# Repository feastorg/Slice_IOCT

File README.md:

# Slice_IOCT

Industrial digital I/O slice for BREAD: four 12–24 V inputs and four
solid-state relay outputs, for sensors and actuators on a 24 V field supply.

An Arduino Nano on the 10-pin slice bus (G3, Slice Interface 1), 70 × 100 mm,
two layers. Hardware revision r2.

## Introduction

The slice works like a small PLC I/O module. Each input reads a field signal
through an optocoupler with a switching threshold; each output is a photo-MOSFET
relay that switches a load from the field supply or acts as a dry contact. A low
level on the bus e-stop line turns every output off in hardware, whatever the
firmware does.

## Usage

### Inputs (J3)

Each input has three terminals: `INx+`, `INx-` and `GND`.

- **Floating (isolated):** connect the sensor's output between `INx+` and
  `INx-`. The source must provide its own return path.
- **Board-referenced:** link `INx-` to the `GND` terminal beside it and drive
  `INx+` against board ground.

An input reads OFF below about 7 V and ON from 11 V; it is rated to 30 V. A
reversed input does no harm. The Nano reads IN1–IN4 on D9, D8, D7 and D6, high
when the input is on.

### Outputs (J2)

Each output has three terminals: `OUTx-`, `OUTx+` and `VF` (VFIELD).

- **Wet contact:** link `VF` to `OUTx+` (the next terminal) and wire the load
  from `OUTx-` to `GND` on J1.
- **Dry contact:** leave `VF` unconnected and use `OUTx+` / `OUTx-` as a DC
  switch, `OUTx+` the more positive, up to 30 V.

Each output is rated 0.7 A and has a unidirectional TVS diode across it (33 V
standoff), which is why the outputs switch DC only. Fit a flyback diode
across an inductive load anyway. The Nano drives OUT1–OUT4 on A0–A3, high to
switch on.

### Field supply (J1) and VFIELD (JP1)

| J1 pin | Use |
| --- | --- |
| 1 | +24 V field supply in |
| 2 | 0 V of the field supply |
| 3, 4 | GND, return for wet-contact loads |

The 24 V input has reverse-polarity protection and a 30 V TVS diode. JP1 picks
where VFIELD comes from:

| JP1 shunt | VFIELD |
| --- | --- |
| 1–2 | the external supply on J1 |
| 2–3 | the bus +12 V |

VFIELD is limited to 2 A in total. Taking it from the bus loads the backplane's
12 V supply.

### E-stop

Bus pin 6 is the e-stop line (5 V = run, low = stop). It gates the relay drive
through Q2, so a stop, or a slice pulled from the bus, turns all four outputs
off. The Nano reads the same line on D2.

## Documentation

See [docs](docs/), including the [r2 revision plan](docs/revision-r2.md).

---

<div align="center">
  
</div>

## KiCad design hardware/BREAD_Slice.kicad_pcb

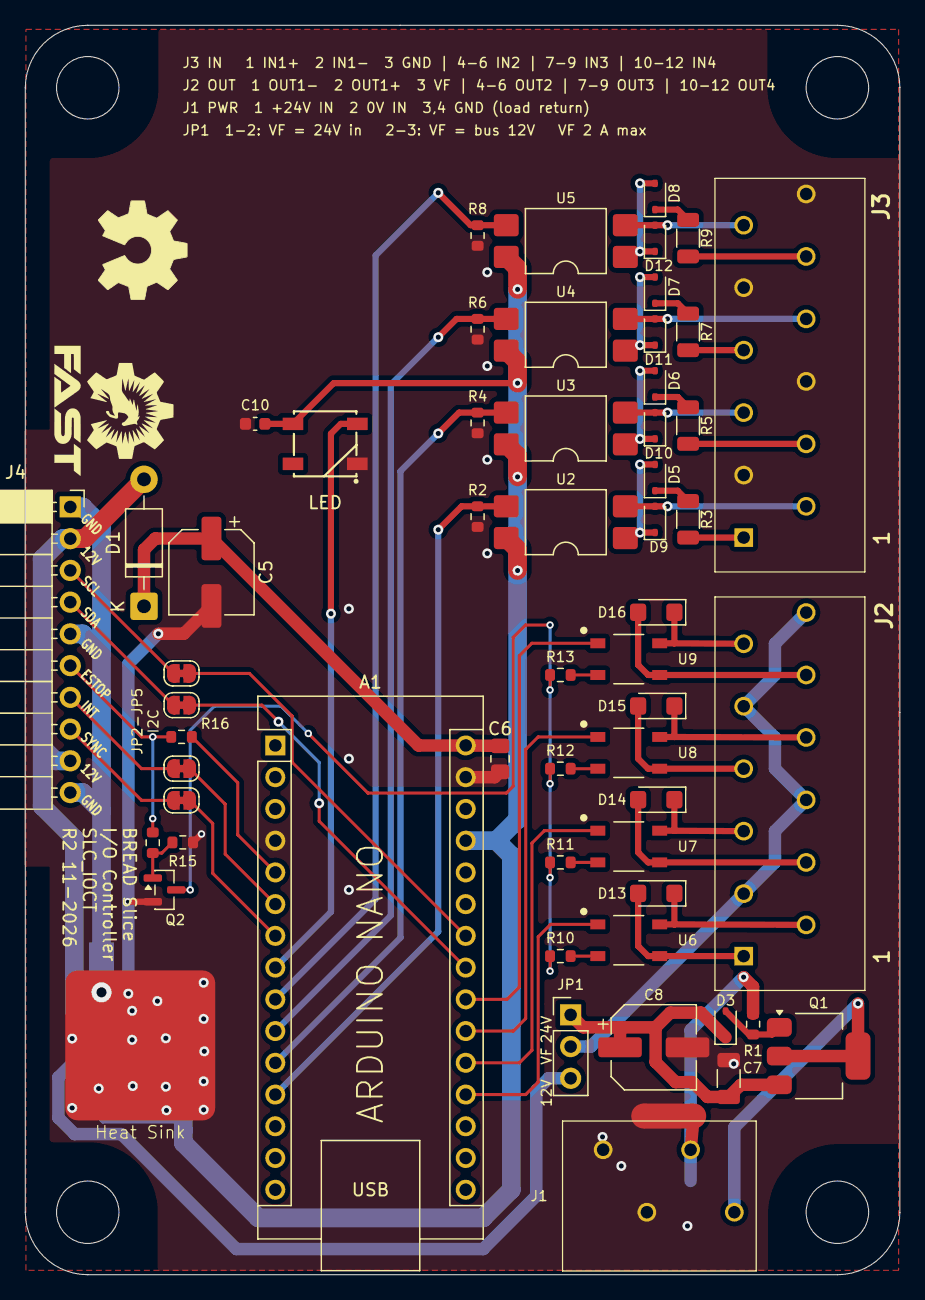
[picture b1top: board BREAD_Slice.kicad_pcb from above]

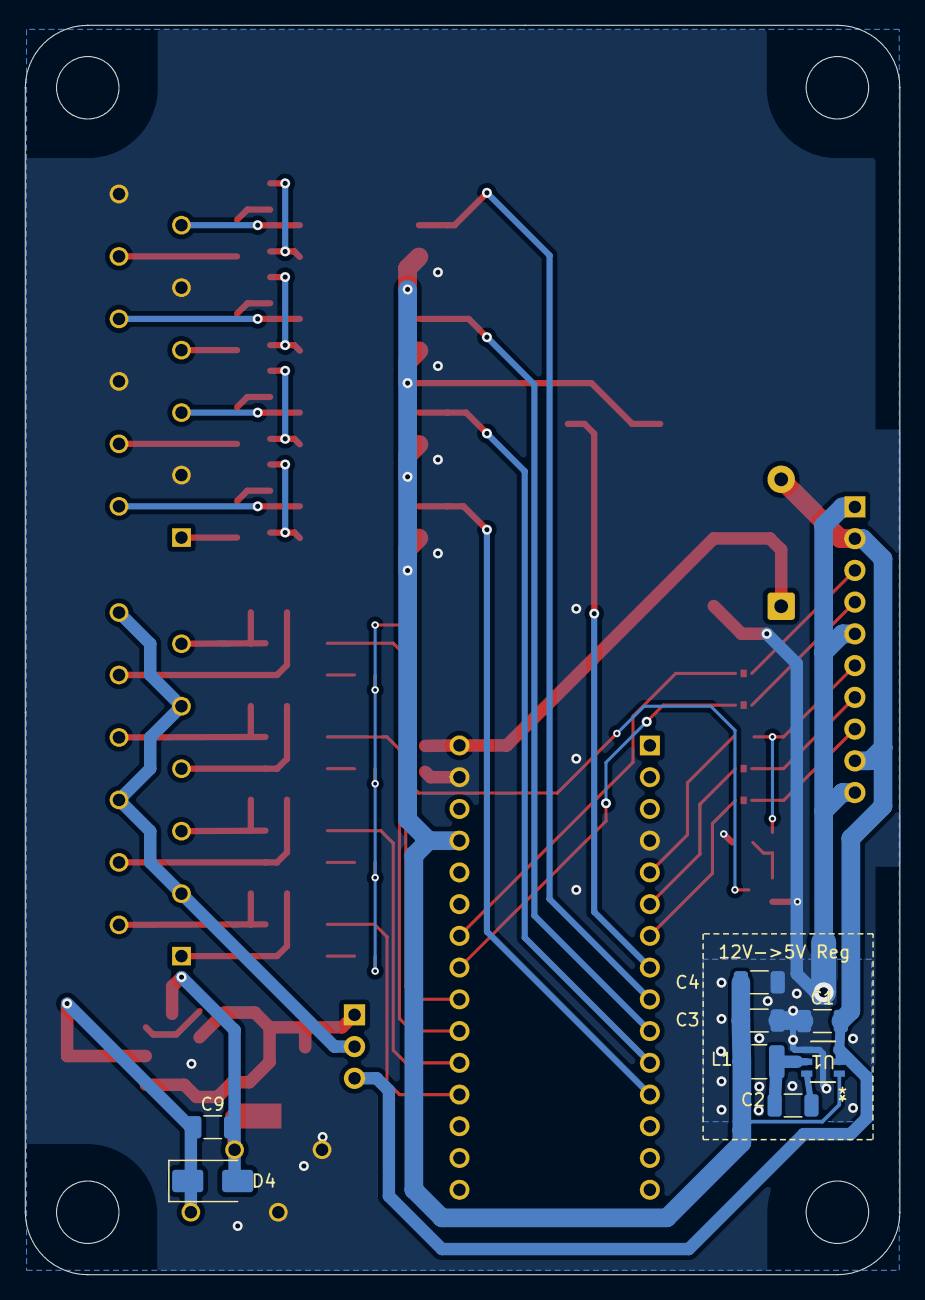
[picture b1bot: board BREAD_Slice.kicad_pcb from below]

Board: 2 copper layers, 70.0 x 100.0 mm, 72 parts (9 on the bottom side), 61 nets.

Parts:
A1: Arduino_Nano_v3.x; Arduino_Nano
C1: 10u 25V; C_1206_3216Metric
C2: 100nF; C_1206_3216Metric
C3, C4: 22u 10V; C_1206_3216Metric
C5: 47u 25V; CP_Elec_6.3x7.7
C6: 0.1u; C_0805_2012Metric_Pad1.18x1.45mm_HandSolder
C7, C9: 100n; C_1206_3216Metric
C8: 10u 63V; CP_Elec_6.3x7.7
C10: 100n; C_0603_1608Metric
D1: 1N4007; D_DO-41_SOD81_P10.16mm_Horizontal
D2: WS2812B_5050; WS2812-5050-4PIN
D3: MM3Z18VT1G; D_SOD-323
D4: SMAJ30CA; D_SMA
D5, D6, D7, D8: MM3Z6V8; D_SOD-323
D9, D10, D11, D12: 1N4148WS; D_SOD-323
D13, D14, D15, D16: SMF33A; D_SMF
H1, H2, H3, H4: MountingHole; MountingHole_5mm
HS1: Heatsink_Pad; Thermal_Pad
J1: 1985218
J2, J3: 1990106
J4: Conn_01x10_Socket; PinSocket_1x10_P2.54mm_Horizontal
JP1: VFIELD source; PinHeader_1x03_P2.54mm_Vertical
JP2: I2C_CLK bus link; SolderJumper-2_P1.3mm_Bridged_RoundedPad1.0x1.5mm
JP3: I2C_DAT bus link; SolderJumper-2_P1.3mm_Bridged_RoundedPad1.0x1.5mm
JP4: INT bus link; SolderJumper-2_P1.3mm_Bridged_RoundedPad1.0x1.5mm
JP5: SYNC bus link; SolderJumper-2_P1.3mm_Bridged_RoundedPad1.0x1.5mm
L1: 4.7uH Isat>=1.4A; L_1210_3225Metric
NT1, NT2: NetTie_2; NetTie-2_SMD_Pad2.0mm
Q1: DMP6023LE; SOT-223-3_TabPin2
Q2: 2N7002; SOT-23
R1, R15: 100k; R_0603_1608Metric
R2, R4, R6, R8: 22k; R_0603_1608Metric
R3, R5, R7, R9: 2.7k; R_1206_3216Metric
R10, R11, R12, R13: 1.3k; R_0603_1608Metric
R14, R16: 1k; R_0603_1608Metric
Ref**: Val**; OSHW_Logo_8mm
U1: AP63205; SOIC_05WU-7_DIO
U2, U3, U4, U5: LTV-817S; SMDIP-4_W9.53mm
U6, U7, U8, U9: G3VM-61VY4

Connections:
+5V: A1.27 (+5V), C3.2, C4.2, C10.1, D2.1 (VDD), L1.2, U1.1 (FB), U2.4, U3.4, U4.4, U5.4
+12V: C1.2, D1.2 (A), J4.2, J4.9, JP1.3, U1.2 (EN), U1.3 (VIN)
/+24V: C7.1, C8.1, D3.1 (K), JP1.1, Q1.3
/ESTOP: J4.6, R14.1, R16.1
/ESTOP_G: Q2.1, R14.2, R15.1
/IN1: A1.12 (D9), R2.1, U2.3
/IN1+: J3.1, R3.2
/IN1-: D9.2, J3.2, U2.2
/IN2: A1.11 (D8), R4.1, U3.3
/IN2+: J3.4, R5.2
/IN2-: D10.2, J3.5, U3.2
/IN3: A1.10 (D7), R6.1, U4.3
/IN3+: J3.7, R7.2
/IN3-: D11.2, J3.8, U4.2
/IN4: A1.9 (D6), R8.1, U5.3
/IN4+: J3.10, R9.2
/IN4-: D12.2, J3.11, U5.2
/Input Power Protection/INPUT_GND: C9.2, D4.2 (A2), J1.2, NT2.2, R1.2
/Input Power Protection/INPUT_VDD: C9.1, D4.1 (A1), J1.1, Q1.2
/Input Power Protection/Q1_G: D3.2 (A), Q1.1, R1.1
/OUT1: A1.19 (A0), U6.1
/OUT1+: D13.1, J2.2, U6.4
/OUT1-: D13.2, J2.1, U6.3
/OUT2: A1.20 (A1), U7.1
/OUT2+: D14.1, J2.5, U7.4
/OUT2-: D14.2, J2.4, U7.3
/OUT3: A1.21 (A2), U8.1
/OUT3+: D15.1, J2.8, U8.4
/OUT3-: D15.2, J2.7, U8.3
/OUT4: A1.22 (A3), U9.1
/OUT4+: D16.1, J2.11, U9.4
/OUT4-: D16.2, J2.10, U9.3
/SSR_RTN: Q2.3, R10.1, R11.1, R12.1, R13.1
/VFIELD: J2.3, J2.6, J2.9, J2.12, JP1.2
/slice_template/I2C_CLK: J4.3, JP2.1
/slice_template/I2C_CLK/A5: A1.24 (A5), JP2.2
/slice_template/I2C_DAT: J4.4, JP3.1
/slice_template/I2C_DAT/A4: A1.23 (A4), JP3.2
/slice_template/INT: J4.7, JP4.1
/slice_template/INT/D3: A1.6 (D3), JP4.2
/slice_template/LED: A1.8 (D5), D2.4 (DIN)
/slice_template/SYNC: J4.8, JP5.1
/slice_template/SYNC/D4: A1.7 (D4), JP5.2
/slice_template/VIN: A1.30 (VIN), C5.1, C6.1, D1.1 (K)
GND: A1.4 (GND), A1.29 (GND), C1.1, C3.1, C4.1, C5.2, C6.2, C7.2, C8.2, C10.2, D2.3 (VSS), HS1.1, J1.3, J1.4, J3.3, J3.6, J3.9, J3.12, NT1.1, NT2.1, Q2.2, R2.2, R4.2, R6.2, R8.2, R15.2, U1.4 (GND)
GNDPWR: J4.1, J4.5, J4.10, NT1.2
unnamed: A1.5 (D2), R16.2
unnamed: D5.2, D9.1, U2.1
unnamed: D5.1, R3.1
unnamed: D6.1, R5.1
unnamed: D7.1, R7.1
unnamed: D8.1, R9.1
unnamed: D6.2, D10.1, U3.1
unnamed: D7.2, D11.1, U4.1
unnamed: D8.2, D12.1, U5.1
unnamed: R10.2, U6.2
unnamed: R11.2, U7.2
unnamed: R12.2, U8.2
unnamed: R13.2, U9.2
unnamed: C2.2, U1.6 (BST)
unnamed: C2.1, L1.1, U1.5 (SW)

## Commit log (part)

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2025-09-28 📄 KiBot index + board renders (auto)
2025-09-28 add plan doc and disable actions for now
2025-11-11 Finished draft 1, still need documentation and review
2025-11-11 remove planning doc move to arch for dispersal later
2025-11-11 remove obsidian metadata
2025-11-11 add obsidian to gitignore
2025-11-11 some revisions and schem and brd
2025-11-11 remove dsstore
2025-11-11 further revision of schem, add subsheets
2025-11-11 add parts list of some terminal options
2025-11-11 update schem
2025-11-12 finalize revision of schematic
2025-11-12 add some more notes to components listing so i can close my tabs out
2025-12-27 Added new conenctor
2025-12-27 updated routing and silkscreen
2026-01-02 go over changes with ian, fix courtyard outline
2026-01-03 fix some footprint links
2026-01-03 remove duplicate in gitignore
2026-01-04 revision of symbol attachment and clear out old layout and start new; kml-custom to kmlib-local
2026-01-05 rerouted using PTSA connectors
2026-01-11 rerouted again with new kml library
2026-02-09 update all to KMLib, untrack backups in gitignore, and revise routing on board to simplify
2026-03-25 added to todo
2026-04-20 refactor: org casing rename from 'FEASTorg' to 'feastorg'
2026-05-20 Add slice.yaml manifest (schema v1.0)
2026-05-22 added dip switches to IOCT
2026-05-22 updated todo
2026-05-24 Add TODO.md with pipeline status
2026-05-24 chore: desc. to readme
2026-05-24 Standardize TODO.md with Pass 1/Pass 2 structure
2026-05-29 added silkscreen for dip switches
